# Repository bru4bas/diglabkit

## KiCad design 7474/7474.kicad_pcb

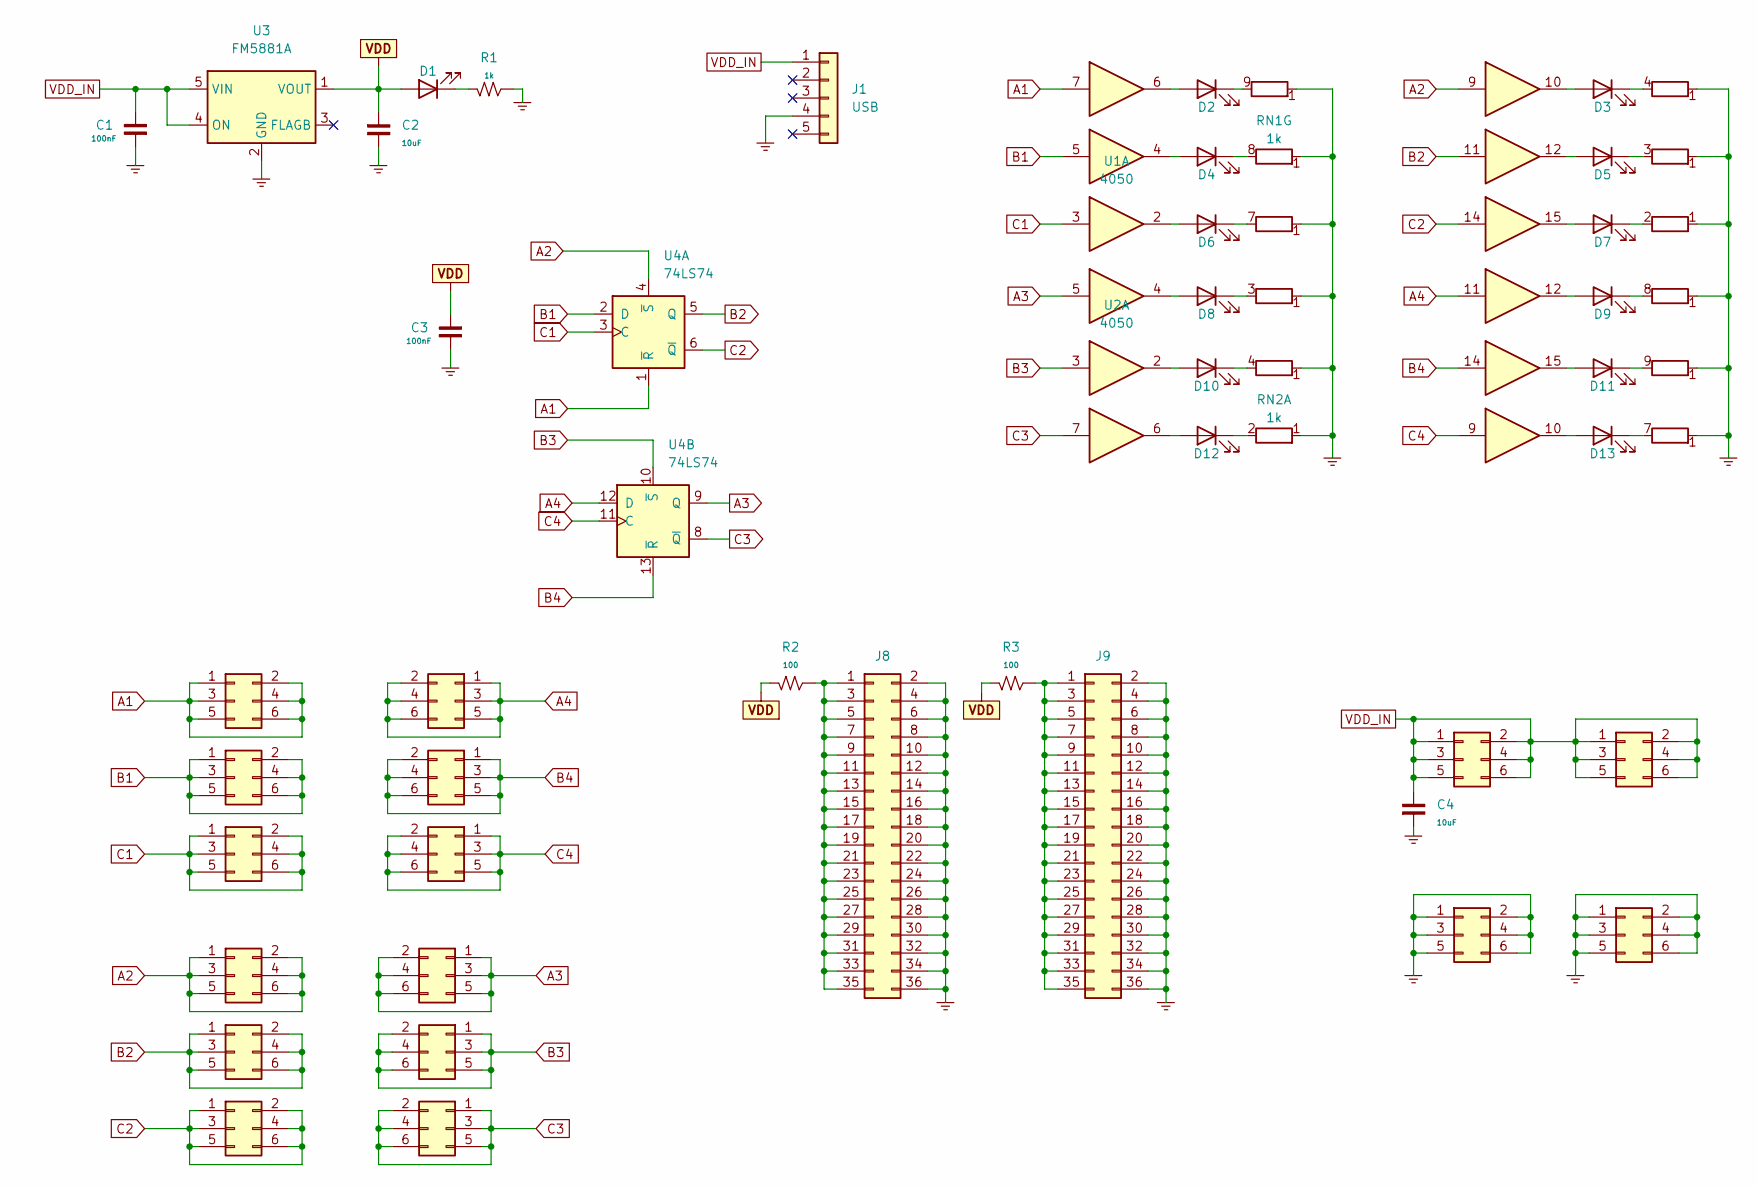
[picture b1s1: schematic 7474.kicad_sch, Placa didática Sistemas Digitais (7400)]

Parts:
C1, C3: 100nF; C_0805_2012Metric
C2, C4: 10uF; C_0805_2012Metric
D1, D2, D3, D4, D5, D6, D7, D8, D9, D10, D11, D12, D13: LED_Small; LED_0805_2012Metric
J1: USB; USB_METALTEX
J2, J3, J4, J5, J6, J7, J10, J11, J12, J13, J14, J15, J16, J17, J18, J19: Conn_02x03_Odd_Even; PinSocket_2x03_P2.54mm_Vertical
J8, J9: Conn_02x18_Odd_Even; PinSocket_2x18_P2.54mm_Vertical
R1: 1k; R_0805_2012Metric
R2, R3: 100; R_0805_2012Metric_Pad1.20x1.40mm_HandSolder
RN1, RN2: 1k; R_Array_SIP9
U1, U2: 4050; SOIC-16_3.9x9.9mm_P1.27mm
U3: FM5881A; SOT-353_SC-70-5
U4: 74LS74

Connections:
A1: J2.1, J2.2, J2.3, J2.4, J2.5, J2.6, U1.7, U4.1 (~R)
A2: J14.1, J14.2, J14.3, J14.4, J14.5, J14.6, U1.9, U4.4 (~S)
A3: J15.1, J15.2, J15.3, J15.4, J15.5, J15.6, U2.5, U4.9 (Q)
A4: J3.1, J3.2, J3.3, J3.4, J3.5, J3.6, U2.11, U4.12 (D)
B1: J6.1, J6.2, J6.3, J6.4, J6.5, J6.6, U1.5, U4.2 (D)
B2: J16.1, J16.2, J16.3, J16.4, J16.5, J16.6, U1.11, U4.5 (Q)
B3: J17.1, J17.2, J17.3, J17.4, J17.5, J17.6, U2.3, U4.10 (~S)
B4: J7.1, J7.2, J7.3, J7.4, J7.5, J7.6, U2.14, U4.13 (~R)
C1: J10.1, J10.2, J10.3, J10.4, J10.5, J10.6, U1.3, U4.3 (C)
C2: J18.1, J18.2, J18.3, J18.4, J18.5, J18.6, U1.14, U4.6 (~Q)
C3: J19.1, J19.2, J19.3, J19.4, J19.5, J19.6, U2.7, U4.8 (~Q)
C4: J11.1, J11.2, J11.3, J11.4, J11.5, J11.6, U2.9, U4.11 (C)
GND: C1.2, C2.1, C3.2, C4.1, J1.4, J8.2, J8.4, J8.6, J8.8, J8.10, J8.12, J8.14, J8.16, J8.18, J8.20, J8.22, J8.24, J8.26, J8.28, J8.30, J8.32, J8.34, J8.36, J9.2, J9.4, J9.6, J9.8, J9.10, J9.12, J9.14, J9.16, J9.18, J9.20, J9.22, J9.24, J9.26, J9.28, J9.30, J9.32, J9.34, J9.36, J12.1, J12.2, J12.3, J12.4, J12.5, J12.6, J13.1, J13.2, J13.3, J13.4, J13.5, J13.6, R1.2, RN1.1 (R1.1), RN2.1 (R1.1), U1.8 (VSS), U2.8 (VSS), U3.2 (GND), U4.7 (GND)
unnamed: D1.1 (K), R1.1
unnamed: D2.1 (K), RN1.9 (R8.2)
unnamed: D2.2 (A), U1.6
unnamed: D3.1 (K), RN1.4 (R3.2)
unnamed: D3.2 (A), U1.10
unnamed: D4.1 (K), RN1.8 (R7.2)
unnamed: D4.2 (A), U1.4
unnamed: D5.1 (K), RN1.3 (R2.2)
unnamed: D5.2 (A), U1.12
unnamed: D6.1 (K), RN1.7 (R6.2)
unnamed: D6.2 (A), U1.2
unnamed: D7.1 (K), RN1.2 (R1.2)
unnamed: D7.2 (A), U1.15
unnamed: D8.1 (K), RN2.3 (R2.2)
unnamed: D8.2 (A), U2.4
unnamed: D9.1 (K), RN2.8 (R7.2)
unnamed: D9.2 (A), U2.12
unnamed: D10.1 (K), RN2.4 (R3.2)
unnamed: D10.2 (A), U2.2
unnamed: D11.1 (K), RN2.9 (R8.2)
unnamed: D11.2 (A), U2.15
unnamed: D12.1 (K), RN2.2 (R1.2)
unnamed: D12.2 (A), U2.6
unnamed: D13.1 (K), RN2.7 (R6.2)
unnamed: D13.2 (A), U2.10
unnamed: J8.1, J8.3, J8.5, J8.7, J8.9, J8.11, J8.13, J8.15, J8.17, J8.19, J8.21, J8.23, J8.25, J8.27, J8.29, J8.31, J8.33, J8.35, R2.2
unnamed: J9.1, J9.3, J9.5, J9.7, J9.9, J9.11, J9.13, J9.15, J9.17, J9.19, J9.21, J9.23, J9.25, J9.27, J9.29, J9.31, J9.33, J9.35, R3.2
VDD: C2.2, C3.1, D1.2 (A), R2.1, R3.1, U1.1 (VCC), U2.1 (VCC), U3.1 (VOUT)
VDD_IN: C1.1, C4.2, J1.1, J4.1, J4.2, J4.3, J4.4, J4.5, J4.6, J5.1, J5.2, J5.3, J5.4, J5.5, J5.6, U3.4 (ON), U3.5 (VIN)

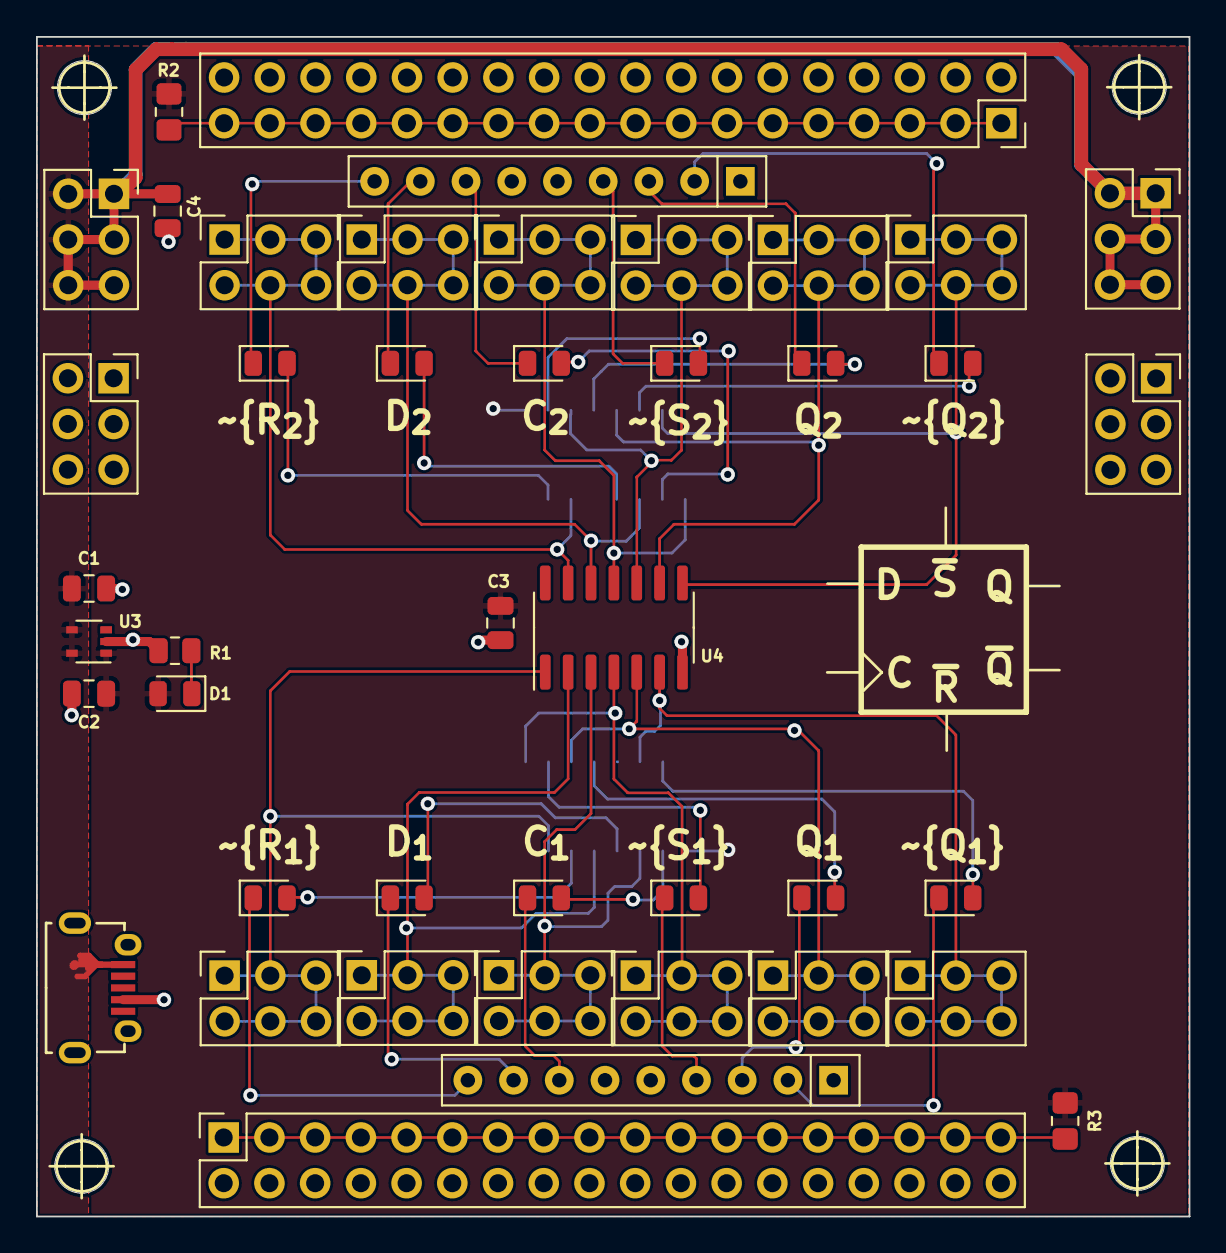
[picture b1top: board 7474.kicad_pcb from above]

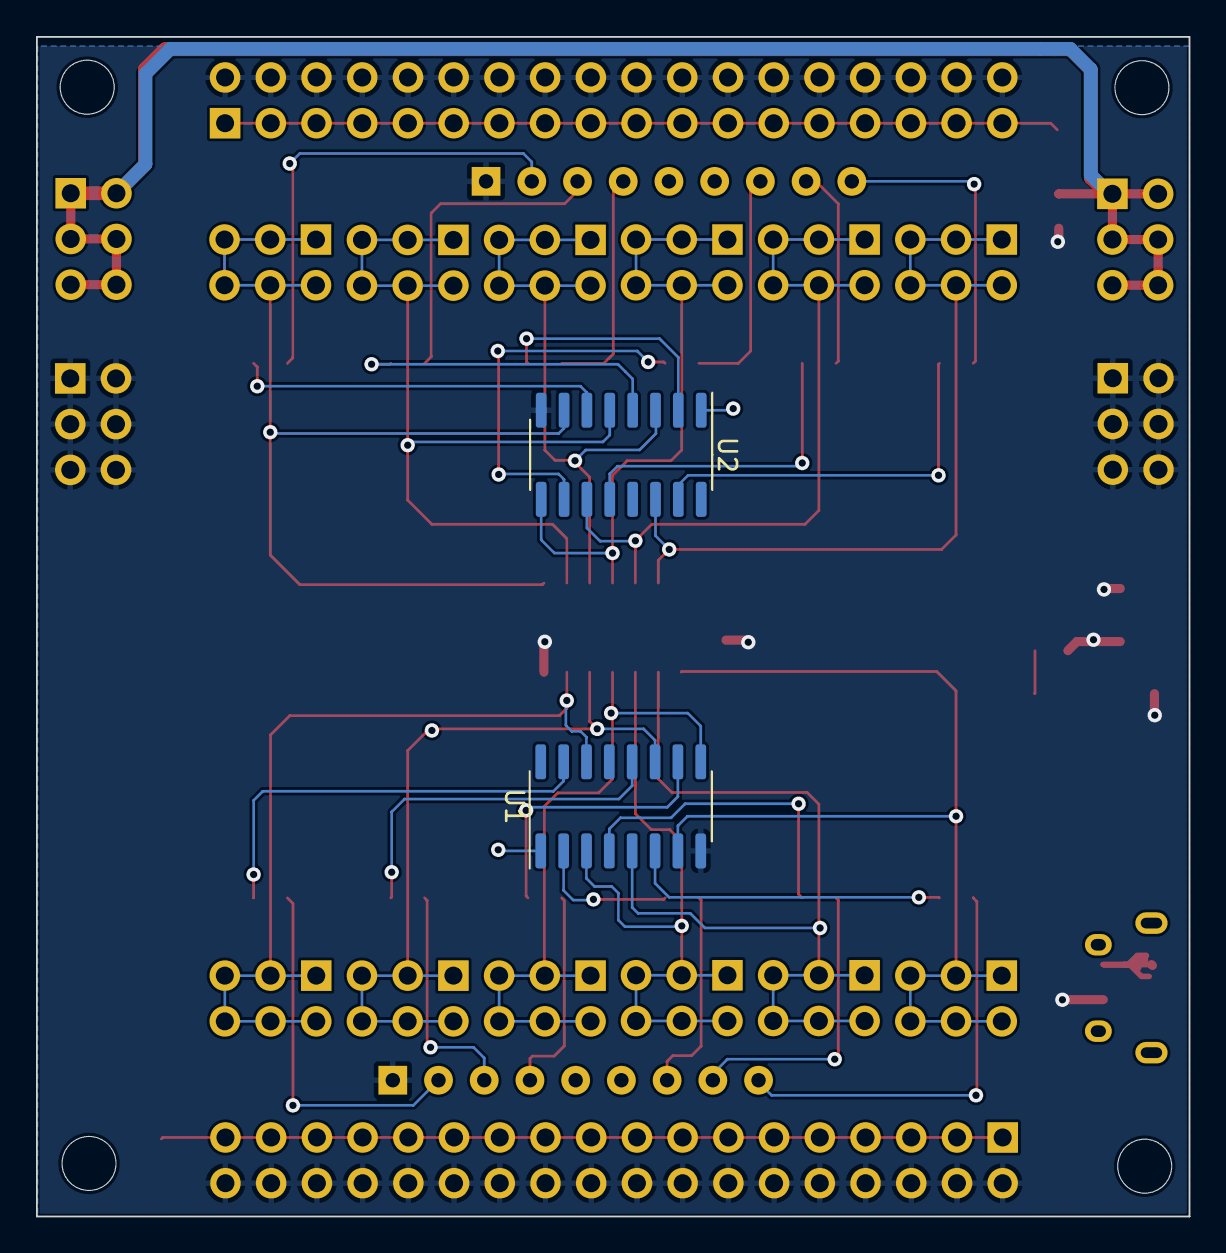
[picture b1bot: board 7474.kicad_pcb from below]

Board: 2 copper layers, 64.0 x 65.5 mm, 45 parts (2 on the bottom side), 42 nets.

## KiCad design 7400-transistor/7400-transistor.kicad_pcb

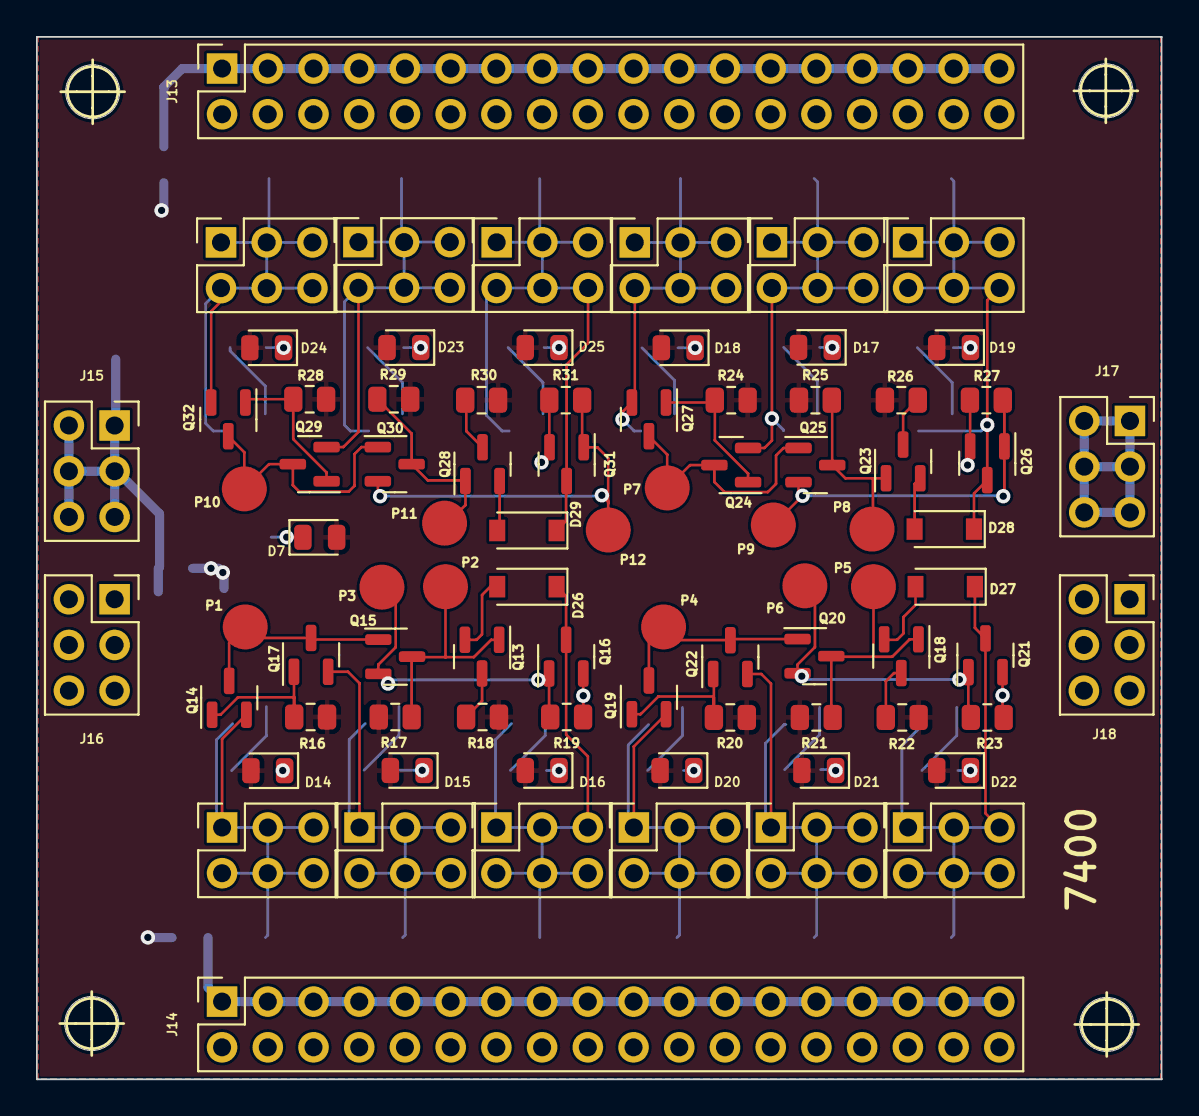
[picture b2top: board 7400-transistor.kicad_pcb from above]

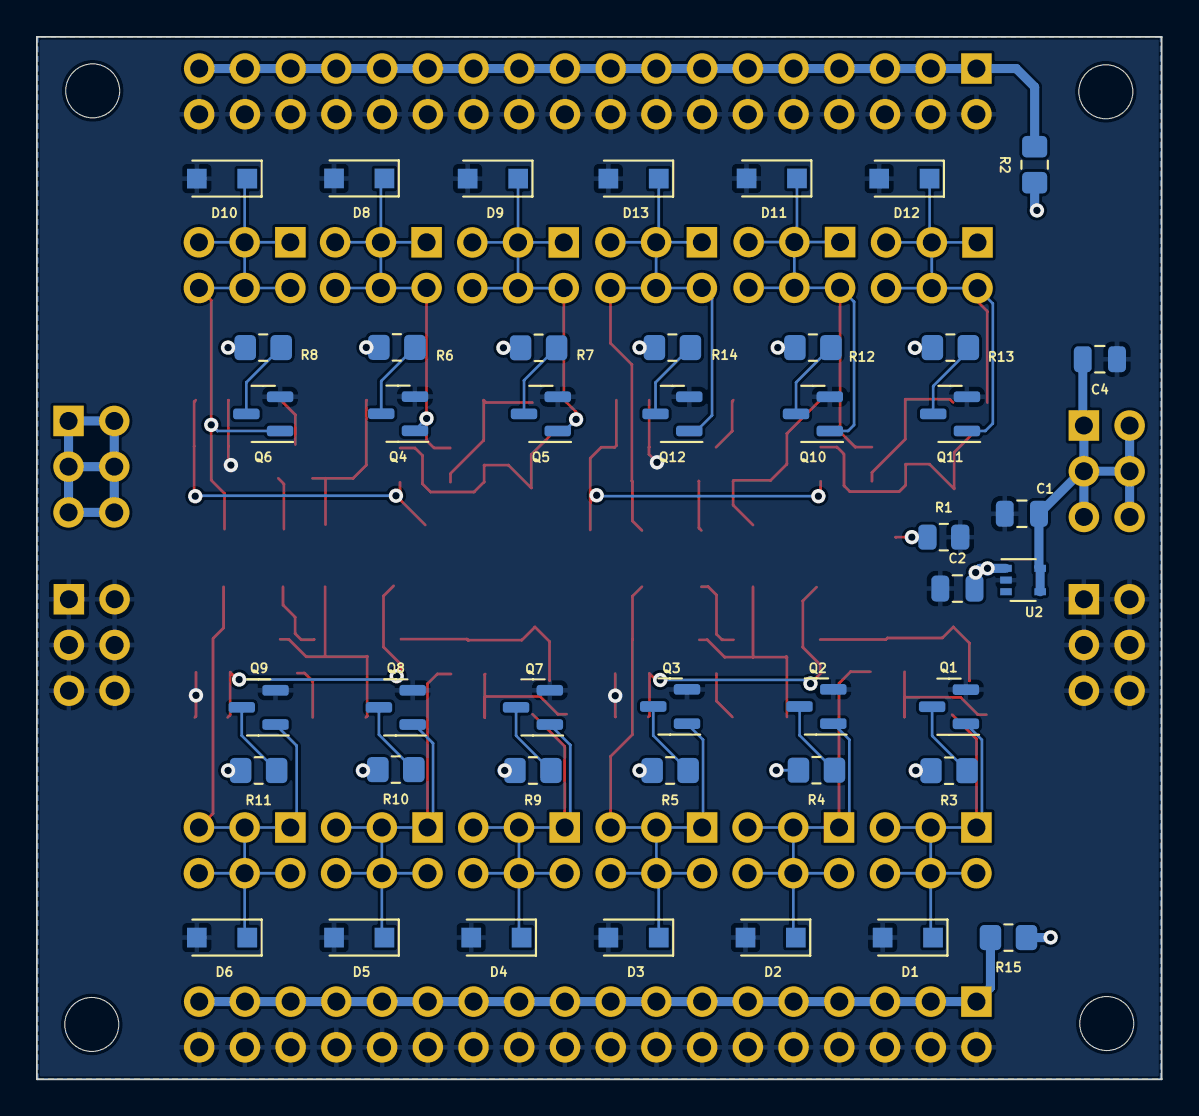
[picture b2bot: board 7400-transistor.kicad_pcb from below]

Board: 2 copper layers, 62.5 x 57.9 mm, 126 parts (43 on the bottom side), 66 nets.

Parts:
C1: 100nF; C_0805_2012Metric
C2, C4: 10uF; C_0805_2012Metric
D1, D2, D3, D4, D5, D6, D8, D9, D10, D11, D12, D13: TVSS_0; D_SOD-123F
D7, D14, D15, D16, D17, D18, D19, D20, D21, D22, D23, D24, D25: LED_Small; LED_0805_2012Metric
D26, D27, D28, D29: D_Small_Filled; D_SOD-123
J1, J2, J3, J4, J5, J6, J7, J8, J9, J10, J11, J12, J15, J16, J17, J18: Conn_02x03_Odd_Even; PinSocket_2x03_P2.54mm_Vertical
J13, J14: Conn_02x18_Odd_Even; PinSocket_2x18_P2.54mm_Vertical
P1, P2, P3, P4, P5, P6, P7, P8, P9, P10, P11, P12: probe
Q1, Q2, Q3, Q4, Q5, Q6, Q7, Q8, Q9, Q10, Q11, Q12: 2N7002; SOT-23
Q13, Q14, Q15, Q16, Q17, Q18, Q19, Q20, Q21, Q22, Q23, Q24, Q25, Q26, Q27, Q28, Q29, Q30, Q31, Q32: BC847; SOT-23
R1: 1k; R_0805_2012Metric
R2, R15: 100; R_0805_2012Metric_Pad1.20x1.40mm_HandSolder
R3, R4, R5, R6, R7, R8, R9, R10, R11, R12, R13, R14: 1k; R_0805_2012Metric_Pad1.20x1.40mm_HandSolder
R16, R20, R24, R28: 40k; R_0805_2012Metric
R17, R21, R25, R29: 20k; R_0805_2012Metric
R18, R22, R26, R30: 500; R_0805_2012Metric
R19, R23, R27, R31: 12k; R_0805_2012Metric
U2: FM5881A; SOT-353_SC-70-5

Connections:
A1: D1.1, J1.1, J1.2, J1.3, J1.4, J1.5, J1.6, Q1.1 (G), Q14.2 (E)
A2: D4.1, J4.1, J4.2, J4.3, J4.4, J4.5, J4.6, Q7.1 (G), Q19.2 (E)
A3: D8.1, J7.1, J7.2, J7.3, J7.4, J7.5, J7.6, Q4.1 (G), Q24.2 (E)
A4: D11.1, J10.1, J10.2, J10.3, J10.4, J10.5, J10.6, Q10.1 (G), Q29.2 (E)
B1: D2.1, J2.1, J2.2, J2.3, J2.4, J2.5, J2.6, Q2.1 (G), Q17.2 (E)
B2: D5.1, J5.1, J5.2, J5.3, J5.4, J5.5, J5.6, Q8.1 (G), Q22.2 (E)
B3: D9.1, J8.1, J8.2, J8.3, J8.4, J8.5, J8.6, Q5.1 (G), Q27.2 (E)
B4: D12.1, J11.1, J11.2, J11.3, J11.4, J11.5, J11.6, Q11.1 (G), Q32.2 (E)
C1: D3.1, D26.1 (K), J3.1, J3.2, J3.3, J3.4, J3.5, J3.6, Q3.1 (G), Q16.3 (C)
C2: D6.1, D27.1 (K), J6.1, J6.2, J6.3, J6.4, J6.5, J6.6, Q9.1 (G), Q21.3 (C)
C3: D10.1, D28.1 (K), J9.1, J9.2, J9.3, J9.4, J9.5, J9.6, Q6.1 (G), Q26.3 (C)
C4: D13.1, D29.1 (K), J12.1, J12.2, J12.3, J12.4, J12.5, J12.6, Q12.1 (G), Q31.3 (C)
GND: C1.2, C2.1, C4.1, D1.2, D2.2, D3.2, D4.2, D5.2, D6.2, D8.2, D9.2, D10.2, D11.2, D12.2, D13.2, J13.2, J13.4, J13.6, J13.8, J13.10, J13.12, J13.14, J13.16, J13.18, J13.20, J13.22, J13.24, J13.26, J13.28, J13.30, J13.32, J13.34, J13.36, J14.2, J14.4, J14.6, J14.8, J14.10, J14.12, J14.14, J14.16, J14.18, J14.20, J14.22, J14.24, J14.26, J14.28, J14.30, J14.32, J14.34, J14.36, J16.1, J16.2, J16.3, J16.4, J16.5, J16.6, J18.1, J18.2, J18.3, J18.4, J18.5, J18.6, Q1.2 (S), Q2.2 (S), Q3.2 (S), Q4.2 (S), Q5.2 (S), Q6.2 (S), Q7.2 (S), Q8.2 (S), Q9.2 (S), Q10.2 (S), Q11.2 (S), Q12.2 (S), Q16.2 (E), Q21.2 (E), Q26.2 (E), Q31.2 (E), R1.2, R19.1, R23.1, R27.1, R31.1, U2.2 (GND)
unnamed: D7.1 (K), R1.1
unnamed: D14.1 (K), R3.2
unnamed: D15.1 (K), R4.2
unnamed: D16.1 (K), R5.2
unnamed: D17.1 (K), R6.2
unnamed: D18.1 (K), R7.2
unnamed: D19.1 (K), R8.2
unnamed: D20.1 (K), R9.2
unnamed: D21.1 (K), R10.2
unnamed: D22.1 (K), R11.2
unnamed: D23.1 (K), R12.2
unnamed: D24.1 (K), R13.2
unnamed: D25.1 (K), R14.2
unnamed: D26.2 (A), Q13.2 (E)
unnamed: D27.2 (A), Q18.2 (E)
unnamed: D28.2 (A), Q23.2 (E)
unnamed: D29.2 (A), Q28.2 (E)
unnamed: J13.1, J13.3, J13.5, J13.7, J13.9, J13.11, J13.13, J13.15, J13.17, J13.19, J13.21, J13.23, J13.25, J13.27, J13.29, J13.31, J13.33, J13.35, R2.2
unnamed: J14.1, J14.3, J14.5, J14.7, J14.9, J14.11, J14.13, J14.15, J14.17, J14.19, J14.21, J14.23, J14.25, J14.27, J14.29, J14.31, J14.33, J14.35, R15.2
unnamed: Q1.3 (D), R3.1
unnamed: Q2.3 (D), R4.1
unnamed: Q3.3 (D), R5.1
unnamed: Q4.3 (D), R6.1
unnamed: Q5.3 (D), R7.1
unnamed: Q6.3 (D), R8.1
unnamed: Q7.3 (D), R9.1
unnamed: Q8.3 (D), R10.1
unnamed: Q9.3 (D), R11.1
unnamed: Q10.3 (D), R12.1
unnamed: Q11.3 (D), R13.1
unnamed: Q12.3 (D), R14.1
unnamed: P2.0, Q13.1 (B), Q15.3 (C), R17.1
unnamed: Q13.3 (C), R18.1
unnamed: Q14.1 (B), Q17.1 (B), R16.1
unnamed: P1.0, Q14.3 (C), Q15.1 (B), Q17.3 (C)
unnamed: P3.0, Q15.2 (E), Q16.1 (B), R19.2
unnamed: P5.0, Q18.1 (B), Q20.3 (C), R21.1
unnamed: Q18.3 (C), R22.1
unnamed: Q19.1 (B), Q22.1 (B), R20.1
unnamed: P4.0, Q19.3 (C), Q20.1 (B), Q22.3 (C)
unnamed: P6.0, Q20.2 (E), Q21.1 (B), R23.2
unnamed: P8.0, Q23.1 (B), Q25.3 (C), R25.1
unnamed: Q23.3 (C), R26.1
unnamed: Q24.1 (B), Q27.1 (B), R24.1
unnamed: P7.0, Q24.3 (C), Q25.1 (B), Q27.3 (C)
unnamed: P9.0, Q25.2 (E), Q26.1 (B), R27.2
unnamed: P11.0, Q28.1 (B), Q30.3 (C), R29.1
unnamed: Q28.3 (C), R30.1
unnamed: Q29.1 (B), Q32.1 (B), R28.1
unnamed: P10.0, Q29.3 (C), Q30.1 (B), Q32.3 (C)
unnamed: P12.0, Q30.2 (E), Q31.1 (B), R31.2
VDD: C2.2, D7.2 (A), D14.2 (A), D15.2 (A), D16.2 (A), D17.2 (A), D18.2 (A), D19.2 (A), D20.2 (A), D21.2 (A), D22.2 (A), D23.2 (A), D24.2 (A), D25.2 (A), R2.1, R15.1, R16.2, R17.2, R18.2, R20.2, R21.2, R22.2, R24.2, R25.2, R26.2, R28.2, R29.2, R30.2, U2.1 (VOUT)
VDD_IN: C1.1, C4.2, J15.1, J15.2, J15.3, J15.4, J15.5, J15.6, J17.1, J17.2, J17.3, J17.4, J17.5, J17.6, U2.4 (ON), U2.5 (VIN)

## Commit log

2022-04-27 First commit with three boards.
2022-06-02 Simplificação do circuito. Inclusão da placa 7474.
